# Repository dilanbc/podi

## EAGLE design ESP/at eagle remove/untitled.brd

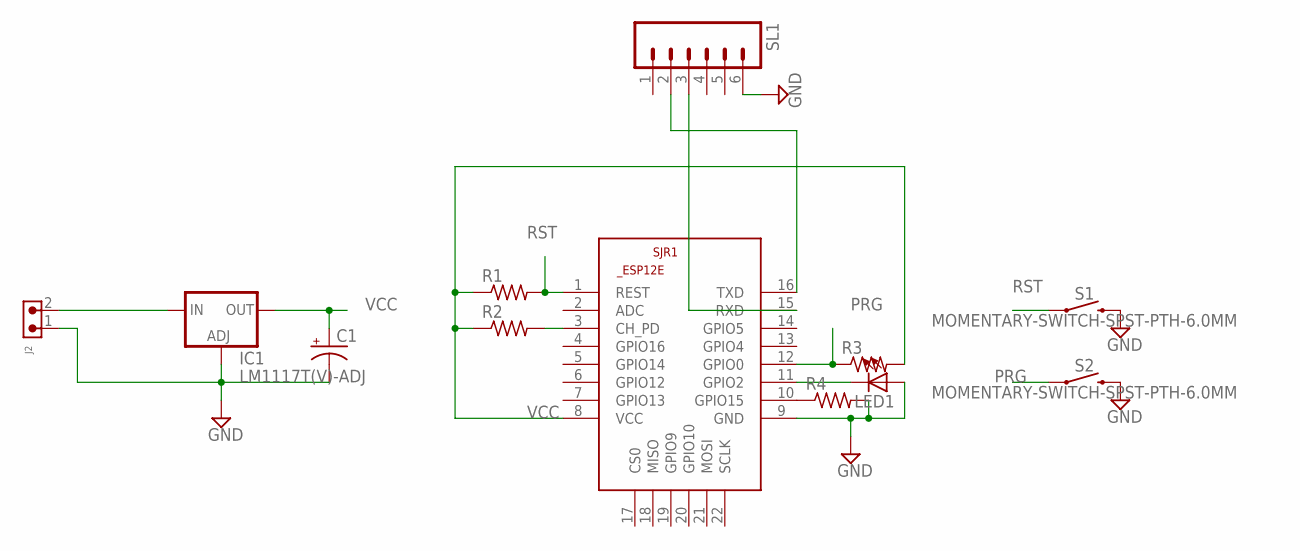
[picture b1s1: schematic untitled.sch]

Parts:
C1: CAPACITOR-PE5-10.5; E5-10,5
IC1: LM1117T(V)-ADJ; TO220V
J2: 691305530002
LED1: LED5MM
R1, R2, R3, R4: R-US_0207/10; 0207/10
S1, S2: MOMENTARY-SWITCH-SPST-PTH-6.0MM; TACTILE_SWITCH_PTH_6.0MM
SJR1: ESP8266-12EESP12E; ESP8266-ESP12E
SL1: M06; 06P

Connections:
GND: C1.-, IC1.1 (ADJ), J2.1, LED1.A, R4.2, S1.3 (2), S2.3 (2), SJR1.9 (GND), SL1.6
unnamed: IC1.3 (IN), J2.2
unnamed: R2.2, SJR1.3 (CH_PD)
unnamed: SJR1.16 (TXD), SL1.2
unnamed: SJR1.15 (RXD), SL1.3
unnamed: LED1.K (C), SJR1.11 (GPIO2)
unnamed: R4.1, SJR1.10 (GPIO15)
PRG: R3.1, S2.1, SJR1.12 (GPIO0)
RST: R1.2, S1.1, SJR1.1 (REST)
VCC: C1.+, IC1.2 (OUT), R1.1, R2.1, R3.2, SJR1.8 (VCC)

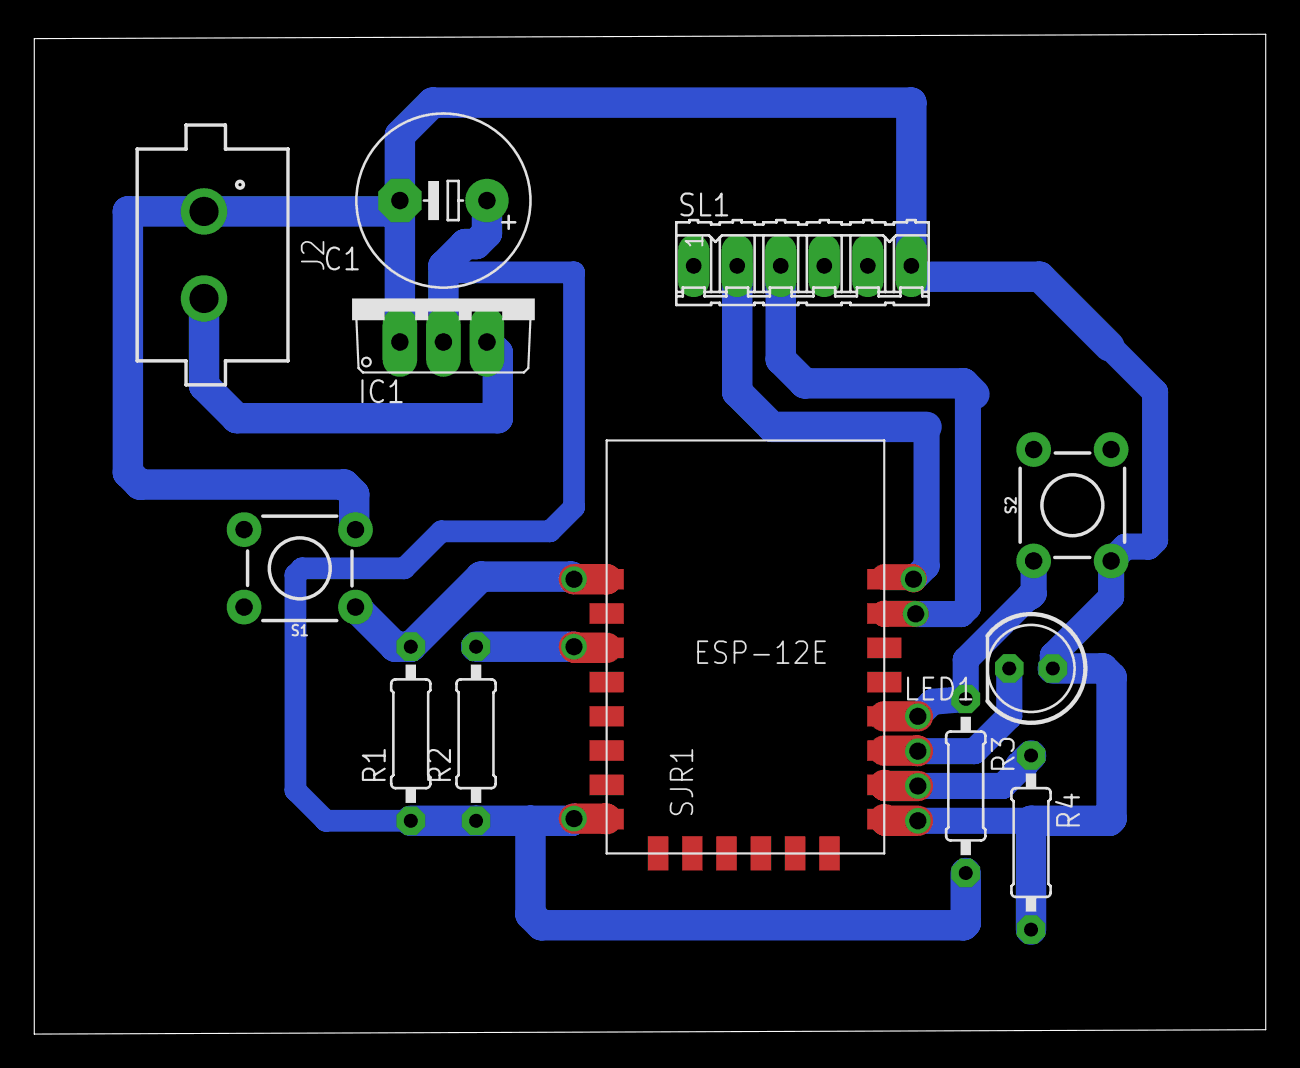
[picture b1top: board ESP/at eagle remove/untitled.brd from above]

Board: 2 copper layers, 71.9 x 58.3 mm, 12 parts (0 on the bottom side), 10 nets.

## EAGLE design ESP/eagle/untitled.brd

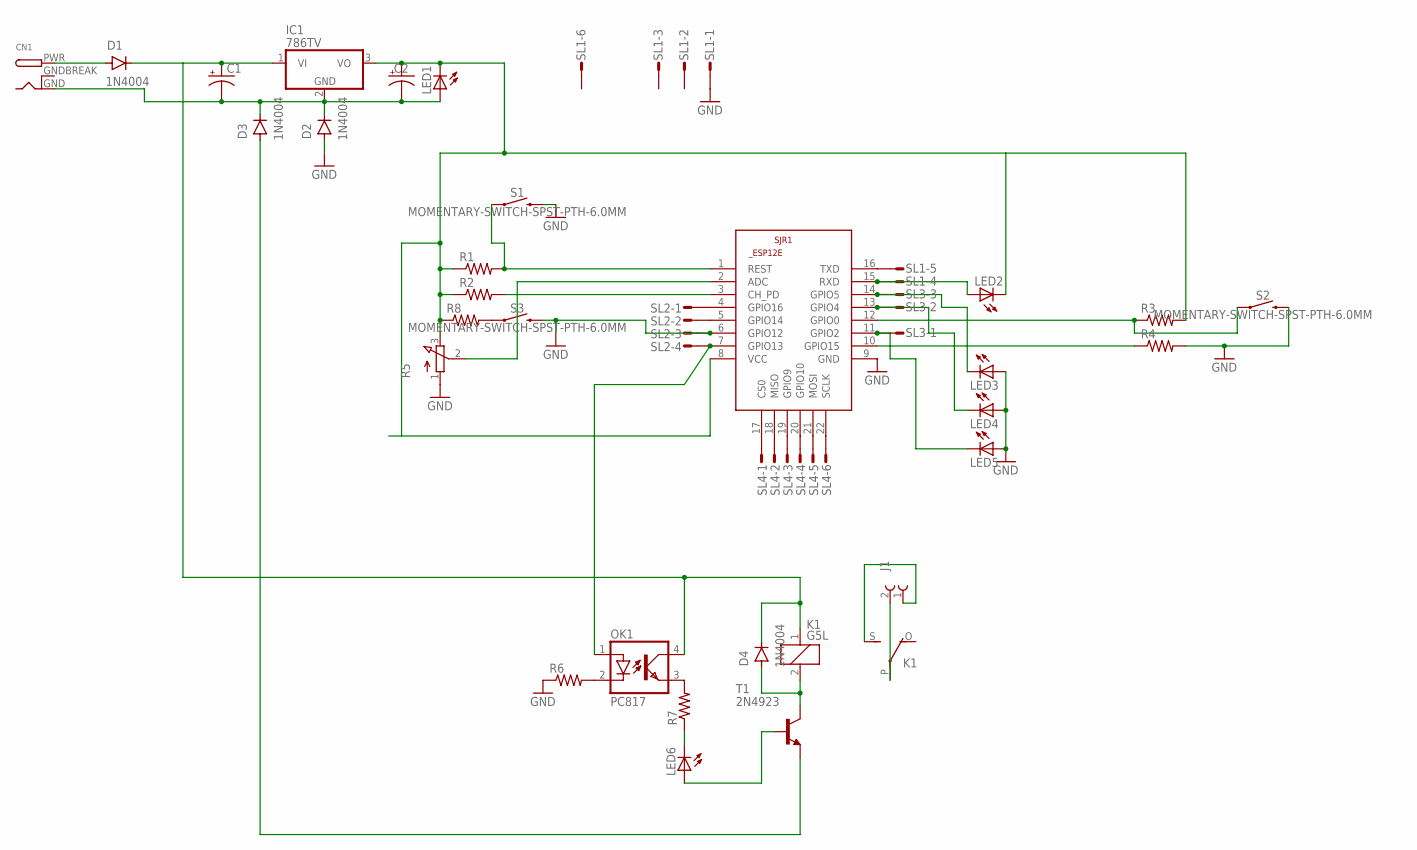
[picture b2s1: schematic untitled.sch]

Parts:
C1, C2: CAPACITOR-PE3.5-8; E3,5-8
CN1: DCBARRELPTH; DCJACK_2MM_PTH
D1, D2, D3, D4: 1N4004; DO-41
IC1: 786TV; TO220V
J1: 691370710002B
K1: G5L; G5LE
LED1, LED2, LED3, LED4, LED5, LED6: LED5MM
OK1: PC817; DIL04
R1, R2, R3, R4, R6, R7, R8: R-US_0309/10; 0309/10
R5: 3RP/1610N
S1, S2, S3: MOMENTARY-SWITCH-SPST-PTH-6.0MM; TACTILE_SWITCH_PTH_6.0MM
SJR1: ESP8266-12EESP12E; ESP8266-ESP12E
SL1, SL4: M06S; 06P
SL2: M04S; 04P
SL3: M03S; 03P
T1: 2N4923; TO126

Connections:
GND: D2.A, LED3.A, LED4.A, LED5.A, R4.2, R5.1 (A), R6.1, S1.3 (2), S2.3 (2), S3.3 (2), SJR1.6 (GPIO12), SJR1.9 (GND), SL1.1, SL2.3
GNDBREAK: CN1.GNDBREAK
unnamed: CN1.PWR, D1.A
unnamed: C1.+, D1.C, D4.C, IC1.1 (VI), K1.1, OK1.4 (COL)
unnamed: C1.-, C2.-, CN1.GND, D2.C, D3.C, IC1.2 (GND), LED1.A
unnamed: C2.+, IC1.3 (VO), LED1.K (C), LED2.K (C), R1.1, R2.1, R3.2, R5.3 (E), R8.1, SJR1.8 (VCC)
unnamed: R3.1, S2.1, SJR1.12 (GPIO0)
unnamed: R2.2, SJR1.3 (CH_PD)
unnamed: R1.2, S1.1, SJR1.1 (REST)
unnamed: R4.1, SJR1.10 (GPIO15)
unnamed: SJR1.16 (TXD), SL1.5
unnamed: LED2.A, SJR1.15 (RXD), SL1.4
unnamed: R5.2 (S), SJR1.2 (ADC)
unnamed: SJR1.4 (GPIO16), SL2.1
unnamed: SJR1.5 (GPIO14), SL2.2
unnamed: OK1.1 (A), SJR1.7 (GPIO13), SL2.4
unnamed: LED3.K (C), SJR1.14 (GPIO5), SL3.3
unnamed: LED4.K (C), SJR1.13 (GPIO4), SL3.2
unnamed: LED5.K (C), SJR1.11 (GPIO2), SL3.1
unnamed: SJR1.17 (CS0), SL4.1
unnamed: SJR1.18 (MISO), SL4.2
unnamed: SJR1.19 (GPIO9), SL4.3
unnamed: SJR1.20 (GPIO10), SL4.4
unnamed: SJR1.21 (MOSI), SL4.5
unnamed: SJR1.22 (SCLK), SL4.6
unnamed: OK1.2 (C), R6.2
unnamed: OK1.3 (EMIT), R7.2
unnamed: D3.A, T1.1 (E)
unnamed: LED6.K (C), R7.1
unnamed: LED6.A, T1.3 (B)
unnamed: J1.2 (1), K1.P
unnamed: D4.A, K1.2, T1.2 (C)
unnamed: J1.1 (2), K1.S
unnamed: R8.2, S3.1

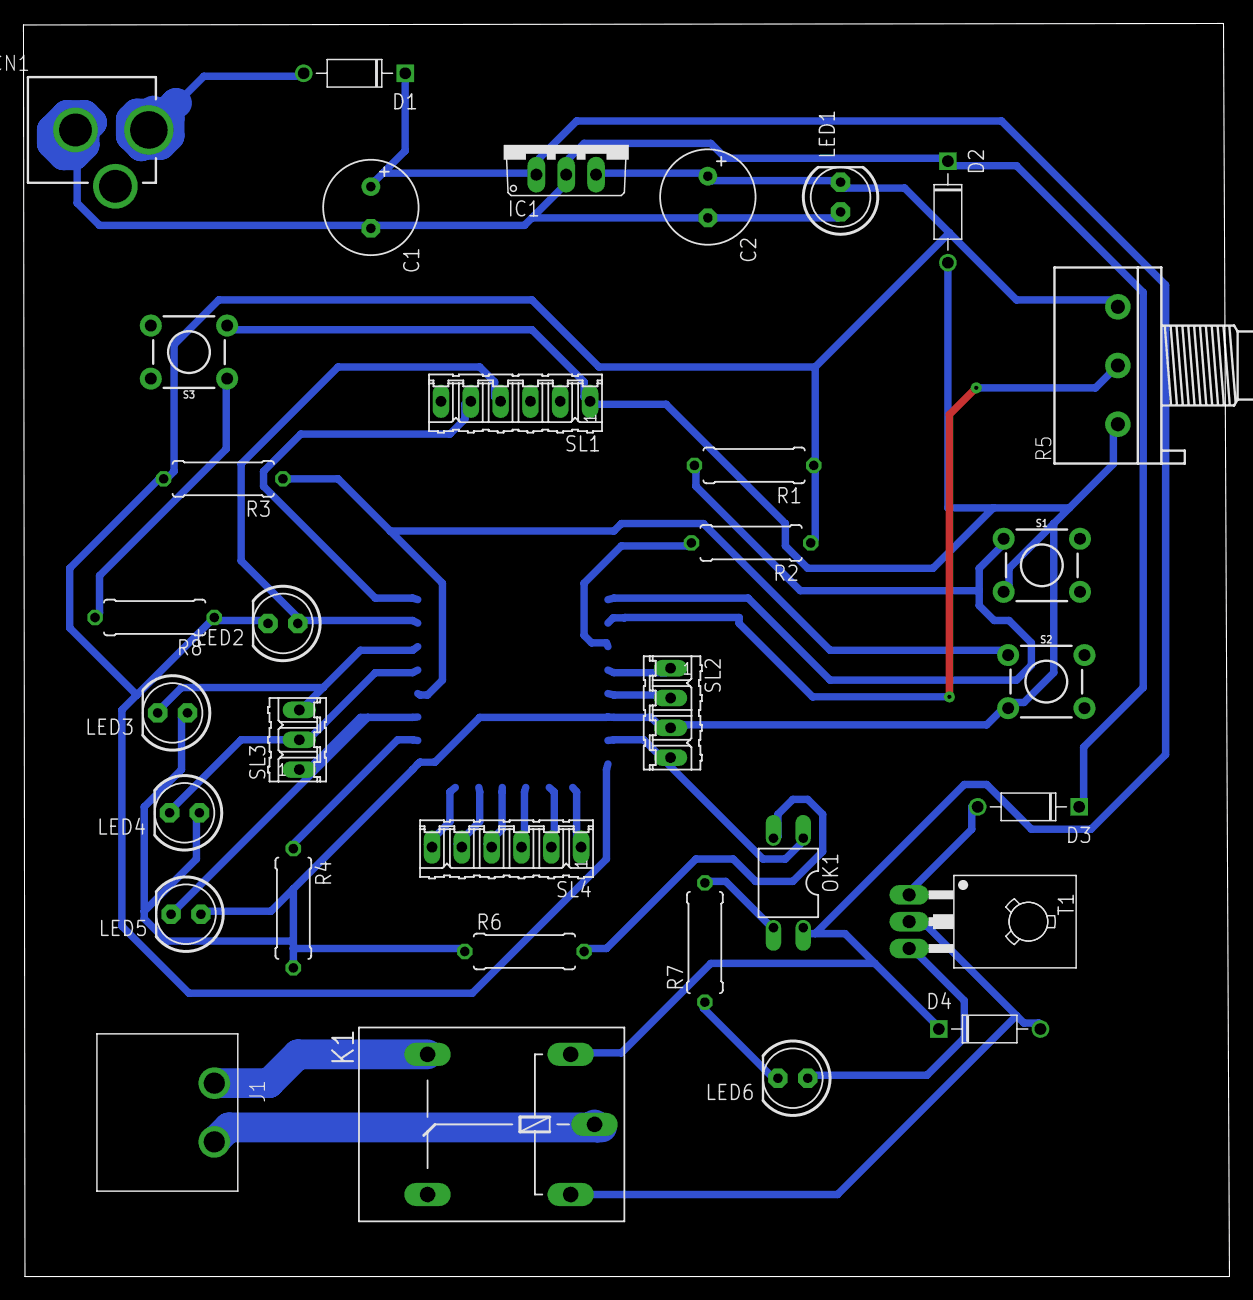
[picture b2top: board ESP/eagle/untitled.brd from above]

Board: 2 copper layers, 102.7 x 106.7 mm, 34 parts (1 on the bottom side), 33 nets.

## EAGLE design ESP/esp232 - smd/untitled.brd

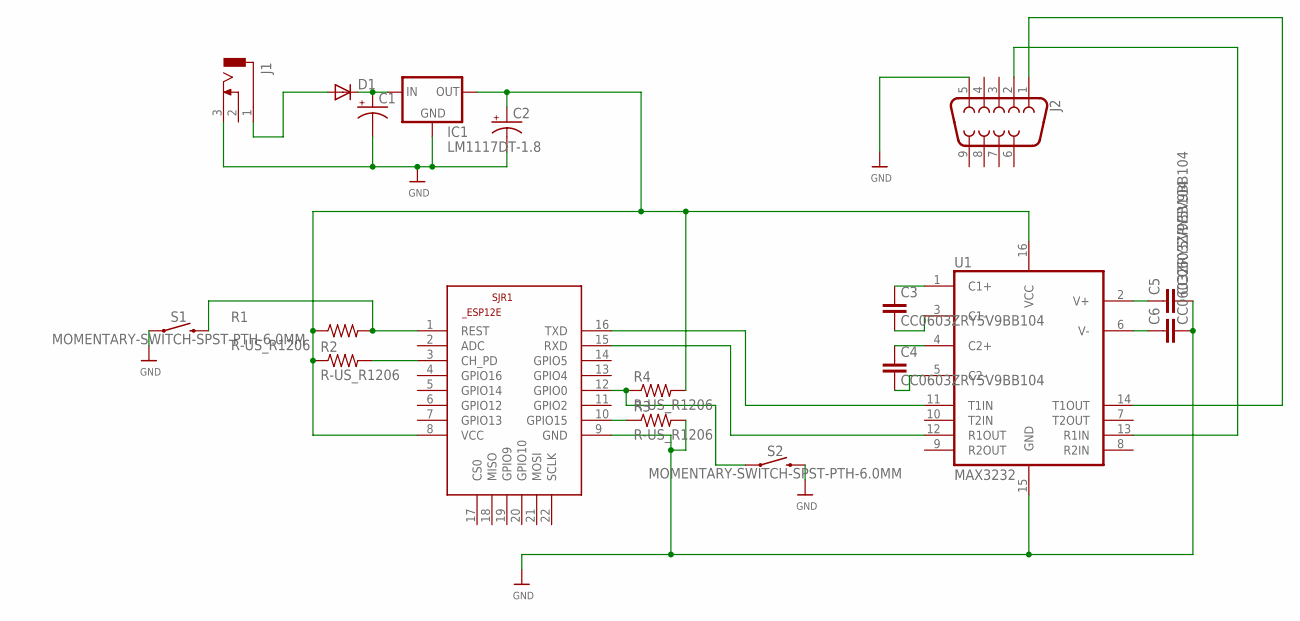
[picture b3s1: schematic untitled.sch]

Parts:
C1, C2: CPOL-US175TMP-0810; 175TMP-0810
C3, C4, C5, C6: CC0603ZRY5V9BB104
D1: DIODESMA; SMADIODE
IC1: LM1117DT-1.8; TO252
J1: DCJ0303
J2: DB9MALE; DB9_MALE
R1, R2, R3, R4: R-US_R1206; R1206
S1, S2: MOMENTARY-SWITCH-SPST-PTH-6.0MM; TACTILE_SWITCH_PTH_6.0MM
SJR1: ESP8266-12EESP12E; ESP8266-ESP12E
U1: MAX3232; SO16

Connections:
GND: C1.-, C2.-, C5.2, C6.2, IC1.1 (GND), J1.3, J2.5, R3.2, S1.1, S2.3 (2), SJR1.9 (GND), U1.15 (GND)
unnamed: R2.2, SJR1.3 (CH_PD)
unnamed: D1.A, J1.1
unnamed: C1.+, D1.C, IC1.2 (IN)
unnamed: R1.2, S1.3 (2), SJR1.1 (REST)
unnamed: R3.1, SJR1.10 (GPIO15)
unnamed: C3.1, U1.1 (C1+)
unnamed: R4.1, S2.1, SJR1.12 (GPIO0)
unnamed: C3.2, U1.3 (C1-)
unnamed: C4.1, U1.4 (C2+)
unnamed: C4.2, U1.5 (C2-)
unnamed: C5.1, U1.2 (V+)
unnamed: C6.1, U1.6 (V-)
unnamed: SJR1.16 (TXD), U1.11 (T1IN)
unnamed: SJR1.15 (RXD), U1.12 (R1OUT)
unnamed: J2.2, U1.13 (R1IN)
unnamed: J2.1, U1.14 (T1OUT)
unnamed: C2.+, IC1.3 (OUT), R1.1, R2.1, R4.2, SJR1.8 (VCC), U1.16 (VCC)

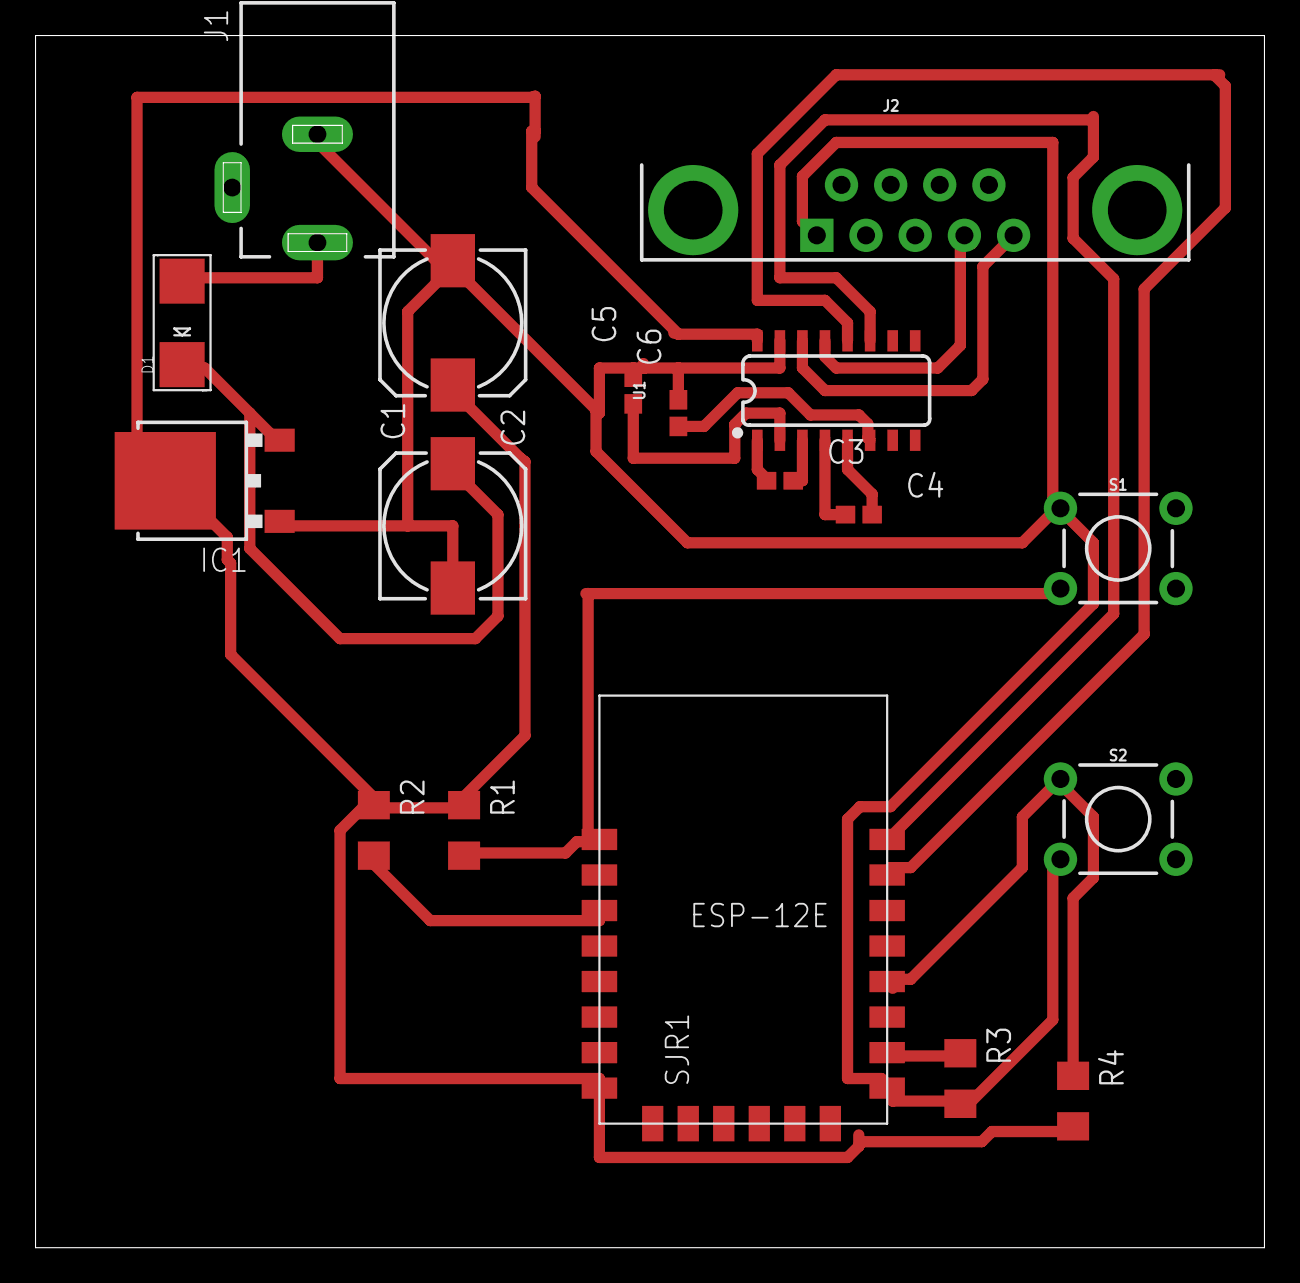
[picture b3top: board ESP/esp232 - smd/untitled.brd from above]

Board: 2 copper layers, 69.2 x 68.2 mm, 18 parts (0 on the bottom side), 18 nets.

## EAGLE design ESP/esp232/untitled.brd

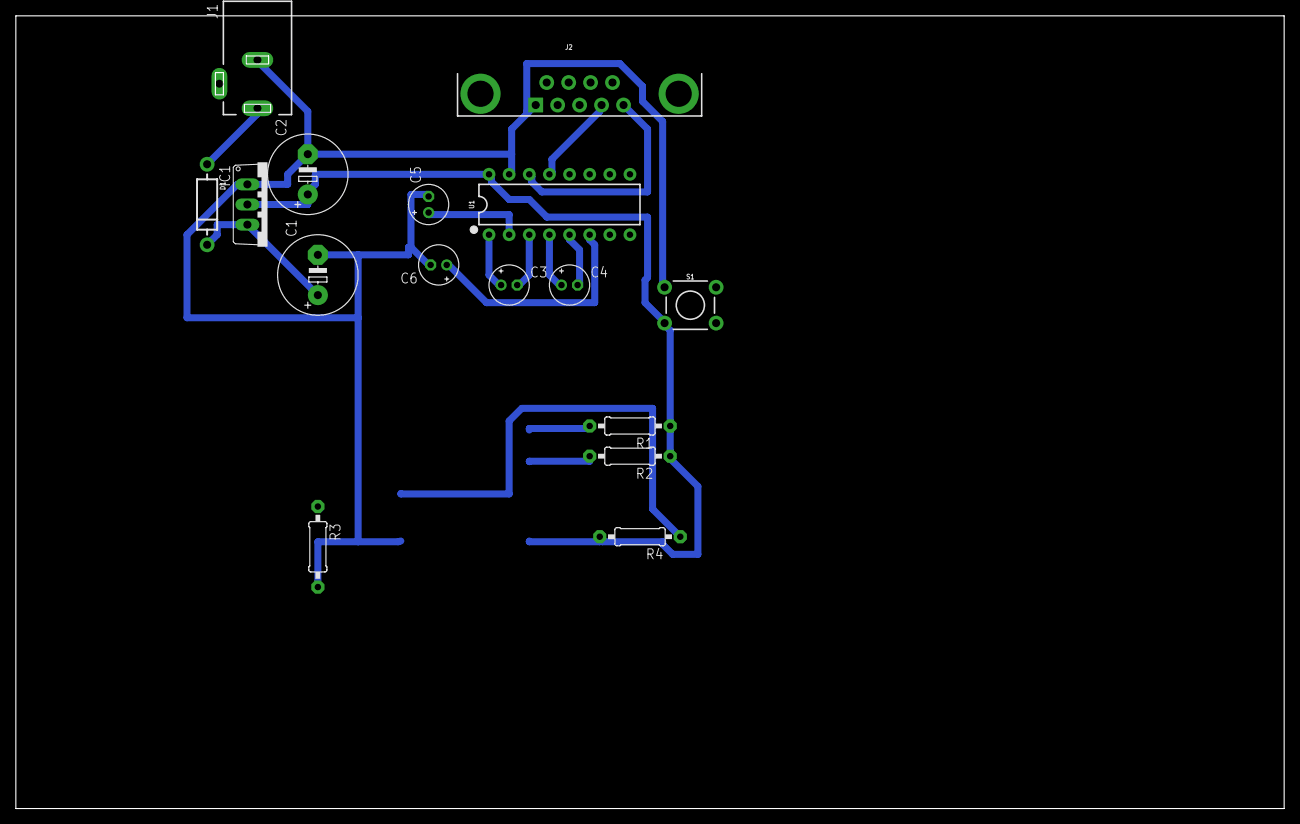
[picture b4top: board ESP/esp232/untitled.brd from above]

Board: 2 copper layers, 160.0 x 100.0 mm, 17 parts (1 on the bottom side), 18 nets.

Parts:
C1, C2: E5-10,5
C3, C4, C5, C6: E2-5
D1: DIODE-1N4001-KIT
IC1: LM1117T(V)-ADJ; TO220V
J1: DCJ0303
J2: DB9_MALE
R1, R2, R3, R4: 0207/10
S1: MOMENTARY-SWITCH-SPST-PTH-6.0MM; TACTILE_SWITCH_PTH_6.0MM
SJR1: ESP8266-ESP12E
U1: MAX3232; DIP16

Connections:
GND: C1.-, C2.-, C5.-, C6.-, IC1.1, J1.3, J2.5, R3.2, S1.1, SJR1.9, U1.15
unnamed: R2.2, SJR1.3
unnamed: D1.A, J1.1
unnamed: C1.+, D1.C, IC1.3
unnamed: C2.+, IC1.2, R1.1, R2.1, R4.2, S1.3, SJR1.8, U1.16
unnamed: R1.2, SJR1.1
unnamed: R3.1, SJR1.10
unnamed: C3.+, U1.1
unnamed: R4.1, SJR1.12
unnamed: C3.-, U1.3
unnamed: C4.+, U1.4
unnamed: C4.-, U1.5
unnamed: C5.+, U1.2
unnamed: C6.+, U1.6
unnamed: SJR1.16, U1.11
unnamed: SJR1.15, U1.12
unnamed: J2.2, U1.13
unnamed: J2.1, U1.14

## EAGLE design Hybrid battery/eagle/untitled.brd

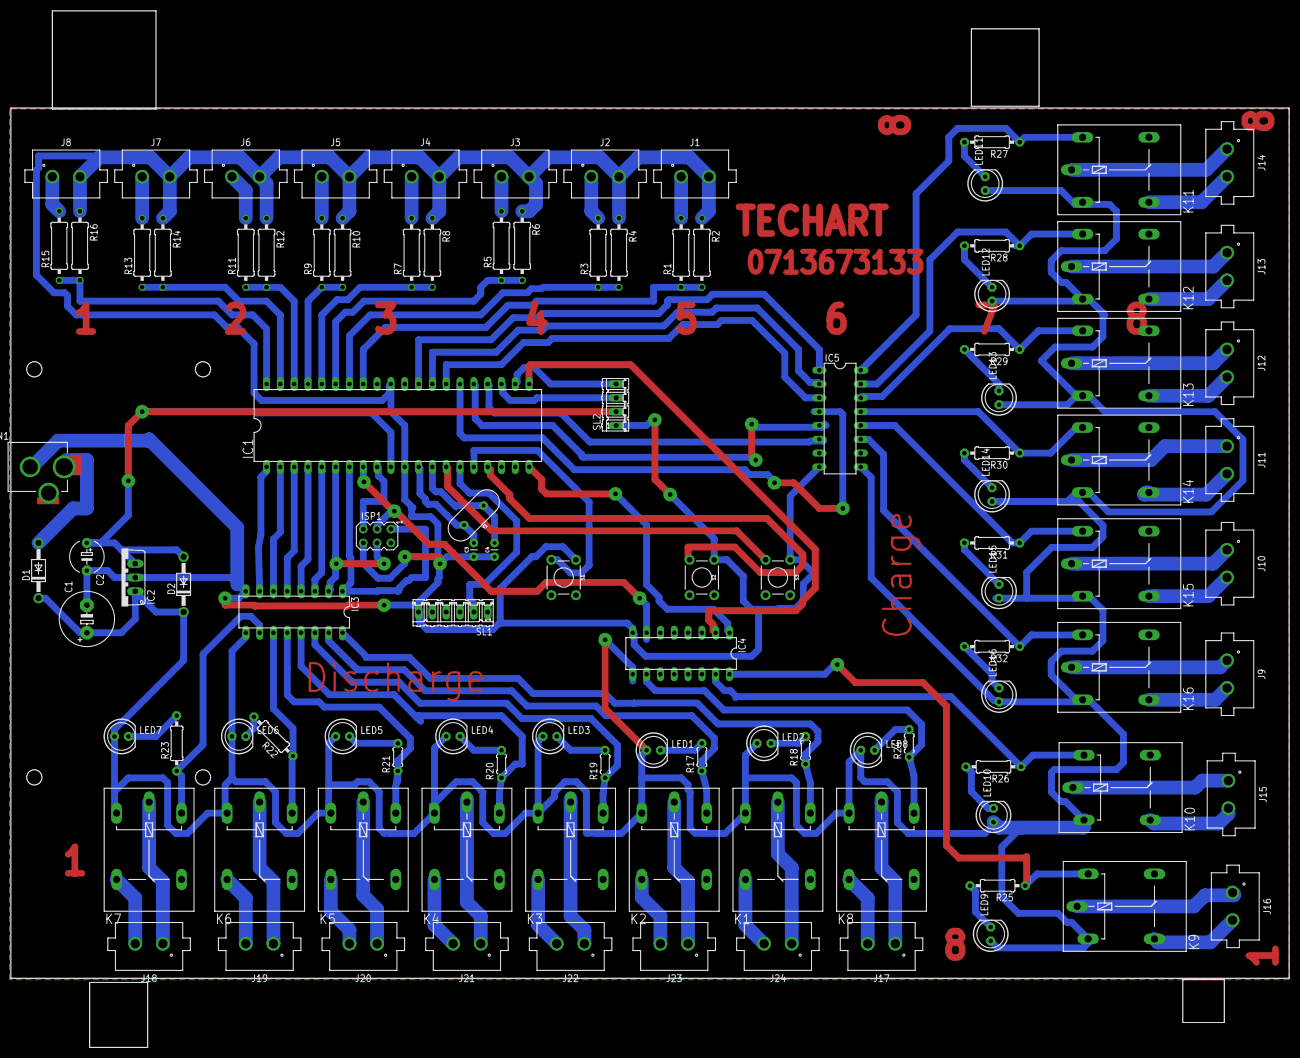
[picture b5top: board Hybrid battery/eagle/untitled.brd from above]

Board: 2 copper layers, 234.9 x 159.9 mm, 107 parts (0 on the bottom side), 109 nets.

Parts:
C1: E5-10,5
C2: E5-6
C3, C4: 22pF; CAP-PTH-2.54
CN1: DCJACK_2MM_PTH
D1, D2: 1N4004; DO41-10
IC1: MEGA16-P; DIL40
IC2: 7805TV; TO220V
IC3, IC4, IC5: ULN2003AN; DIL16
ISP1: AVRISP-6; AVRISP
J1, J2, J3, J4, J5, J6, J7, J8, J9, J10, J11, J12, J13, J14, J15, J16, J17, J18, J19, J20, J21, J22, J23, J24: 691305530002
K1, K2, K3, K4, K5, K6, K7, K8, K9, K10, K11, K12, K13, K14, K15, K16: G5L; G5LE
LED1, LED2, LED3, LED4, LED5, LED6, LED7, LED8, LED9, LED10, LED11, LED12, LED13, LED14, LED15, LED16: LED5MM
R1, R2, R3, R4, R5, R6, R7, R8, R9, R10, R11, R12, R13, R14, R15, R16: 0309/12
R17, R18, R19, R20, R21, R24: 0204/5
R22, R23, R25, R26, R27, R28, R29, R30, R31, R32: 0207/10
S1, S2, S3: MOMENTARY-SWITCH-SPST-PTH-6.0MM-KIT; TACTILE_SWITCH_PTH_6.0MM_KIT
SL1: 06P
SL2: 04P
Y1: 16MHz; HC49US

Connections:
CH0: IC1.20, IC4.1
CH1: IC1.21, IC4.2
CH2: IC1.24, IC5.6
CH3: IC1.25, IC5.5
CH4: IC1.26, IC5.4
CH5: IC1.27, IC5.3
CH6: IC1.28, IC5.2
CH7: IC1.29, IC5.1
DS0: IC1.1, IC3.7
DS1: IC1.2, IC3.6
DS2: IC1.3, IC3.5
DS3: IC1.4, IC3.4
DS4: IC1.5, IC3.3
GND: C1.-, C2.-, C3.1, C4.1, CN1.GND, IC1.11, IC1.31, IC2.2, IC3.8, IC4.8, IC5.8, ISP1.6, J1.2, J2.2, J3.2, J4.2, J5.2, J6.2, J7.2, J8.2, R2.1, R4.1, R6.1, R8.1, R10.1, R12.1, R14.1, R16.1, S1.1, S2.1, S3.1, SL1.6, SL2.1
MISO: IC1.7, IC3.1, ISP1.1
MOSI: IC1.6, IC3.2, ISP1.4
unnamed: C2.+, D2.A, IC1.10, IC2.3, SL2.2
unnamed: C1.+, D1.C, D2.C, IC2.1, IC3.9, IC4.9, IC5.9, K1.1, K2.1, K3.1, K4.1, K5.1, K6.1, K7.1, K8.1, K9.1, K10.1, K11.1, K12.1, K13.1, K14.1, K15.1, K16.1, LED1.A, LED2.A, LED3.A, LED4.A, LED5.A, LED6.A, LED7.A, LED8.A, LED9.A, LED10.A, LED11.A, LED12.A, LED13.A, LED14.A, LED15.A, LED16.A
unnamed: IC1.16, S1.3
unnamed: IC1.23, SL2.3
unnamed: C3.2, IC1.12, Y1.2
unnamed: C4.2, IC1.13, Y1.1
unnamed: IC1.22, SL2.4
unnamed: J1.1, R1.2
unnamed: IC1.17, S2.3
unnamed: IC4.10, K8.2, R24.1
unnamed: IC1.33, R1.1, R2.2
unnamed: J2.1, R3.2
unnamed: IC1.34, R3.1, R4.2
unnamed: J3.1, R5.2
unnamed: IC1.35, R5.1, R6.2
unnamed: J4.1, R7.2
unnamed: IC1.36, R7.1, R8.2
unnamed: J5.1, R9.2
unnamed: J6.1, R11.2
unnamed: IC1.38, R11.1, R12.2
unnamed: J7.1, R13.2
unnamed: IC1.39, R13.1, R14.2
unnamed: J8.1, R15.2
unnamed: IC1.40, R15.1, R16.2
unnamed: IC1.37, R9.1, R10.2
unnamed: IC1.14, S3.3
unnamed: IC4.16, K9.2, R25.1
unnamed: IC4.15, K10.2, R26.1
unnamed: IC5.16, K11.2, R27.1
unnamed: IC5.12, K15.2, R31.1
unnamed: IC3.16, K1.2, R18.1
unnamed: IC3.15, K2.2, R17.1
unnamed: IC3.14, K3.2, R19.1
unnamed: IC3.13, K4.2, R20.1
unnamed: IC3.12, K5.2, R21.1
unnamed: IC3.11, K6.2, R22.1
unnamed: IC3.10, K7.2, R23.1
unnamed: IC5.13, K14.2, R30.1
unnamed: IC5.14, K13.2, R29.1
unnamed: IC5.15, K12.2, R28.1
unnamed: IC5.11, K16.2, R32.1
unnamed: J9.2, K16.S
unnamed: J9.1, K16.P
unnamed: J10.1, K15.P
unnamed: J10.2, K15.S
unnamed: J11.1, K14.P
unnamed: J11.2, K14.S
unnamed: J12.1, K13.P
unnamed: J12.2, K13.S
unnamed: J13.1, K12.P
unnamed: CN1.PWR, D1.A
unnamed: J13.2, K12.S
unnamed: J14.1, K11.P
unnamed: J14.2, K11.S
unnamed: J15.1, K10.P
unnamed: J15.2, K10.S
unnamed: J16.1, K9.P
unnamed: J16.2, K9.S
unnamed: J17.1, K8.P
unnamed: J17.2, K8.S
unnamed: J18.1, K7.P
unnamed: J18.2, K7.S
unnamed: J19.1, K6.P
unnamed: J19.2, K6.S
unnamed: J20.1, K5.P
unnamed: J20.2, K5.S
unnamed: J21.1, K4.P
unnamed: J21.2, K4.S
unnamed: J22.1, K3.P
unnamed: J22.2, K3.S
unnamed: J23.1, K2.P
unnamed: J23.2, K2.S
unnamed: J24.1, K1.P
unnamed: J24.2, K1.S
unnamed: LED2.K, R18.2
unnamed: LED1.K, R17.2
unnamed: LED3.K, R19.2
unnamed: LED4.K, R20.2
unnamed: LED5.K, R21.2
unnamed: LED6.K, R22.2
unnamed: LED7.K, R23.2
unnamed: LED8.K, R24.2
unnamed: LED9.K, R25.2
unnamed: LED10.K, R26.2
unnamed: LED11.K, R27.2
unnamed: LED12.K, R28.2
unnamed: LED13.K, R29.2
unnamed: LED14.K, R30.2
unnamed: LED15.K, R31.2
unnamed: LED16.K, R32.2
RST: IC1.9, ISP1.5
SCK: IC1.8, IC4.7, ISP1.3
TX: IC1.15, SL1.2

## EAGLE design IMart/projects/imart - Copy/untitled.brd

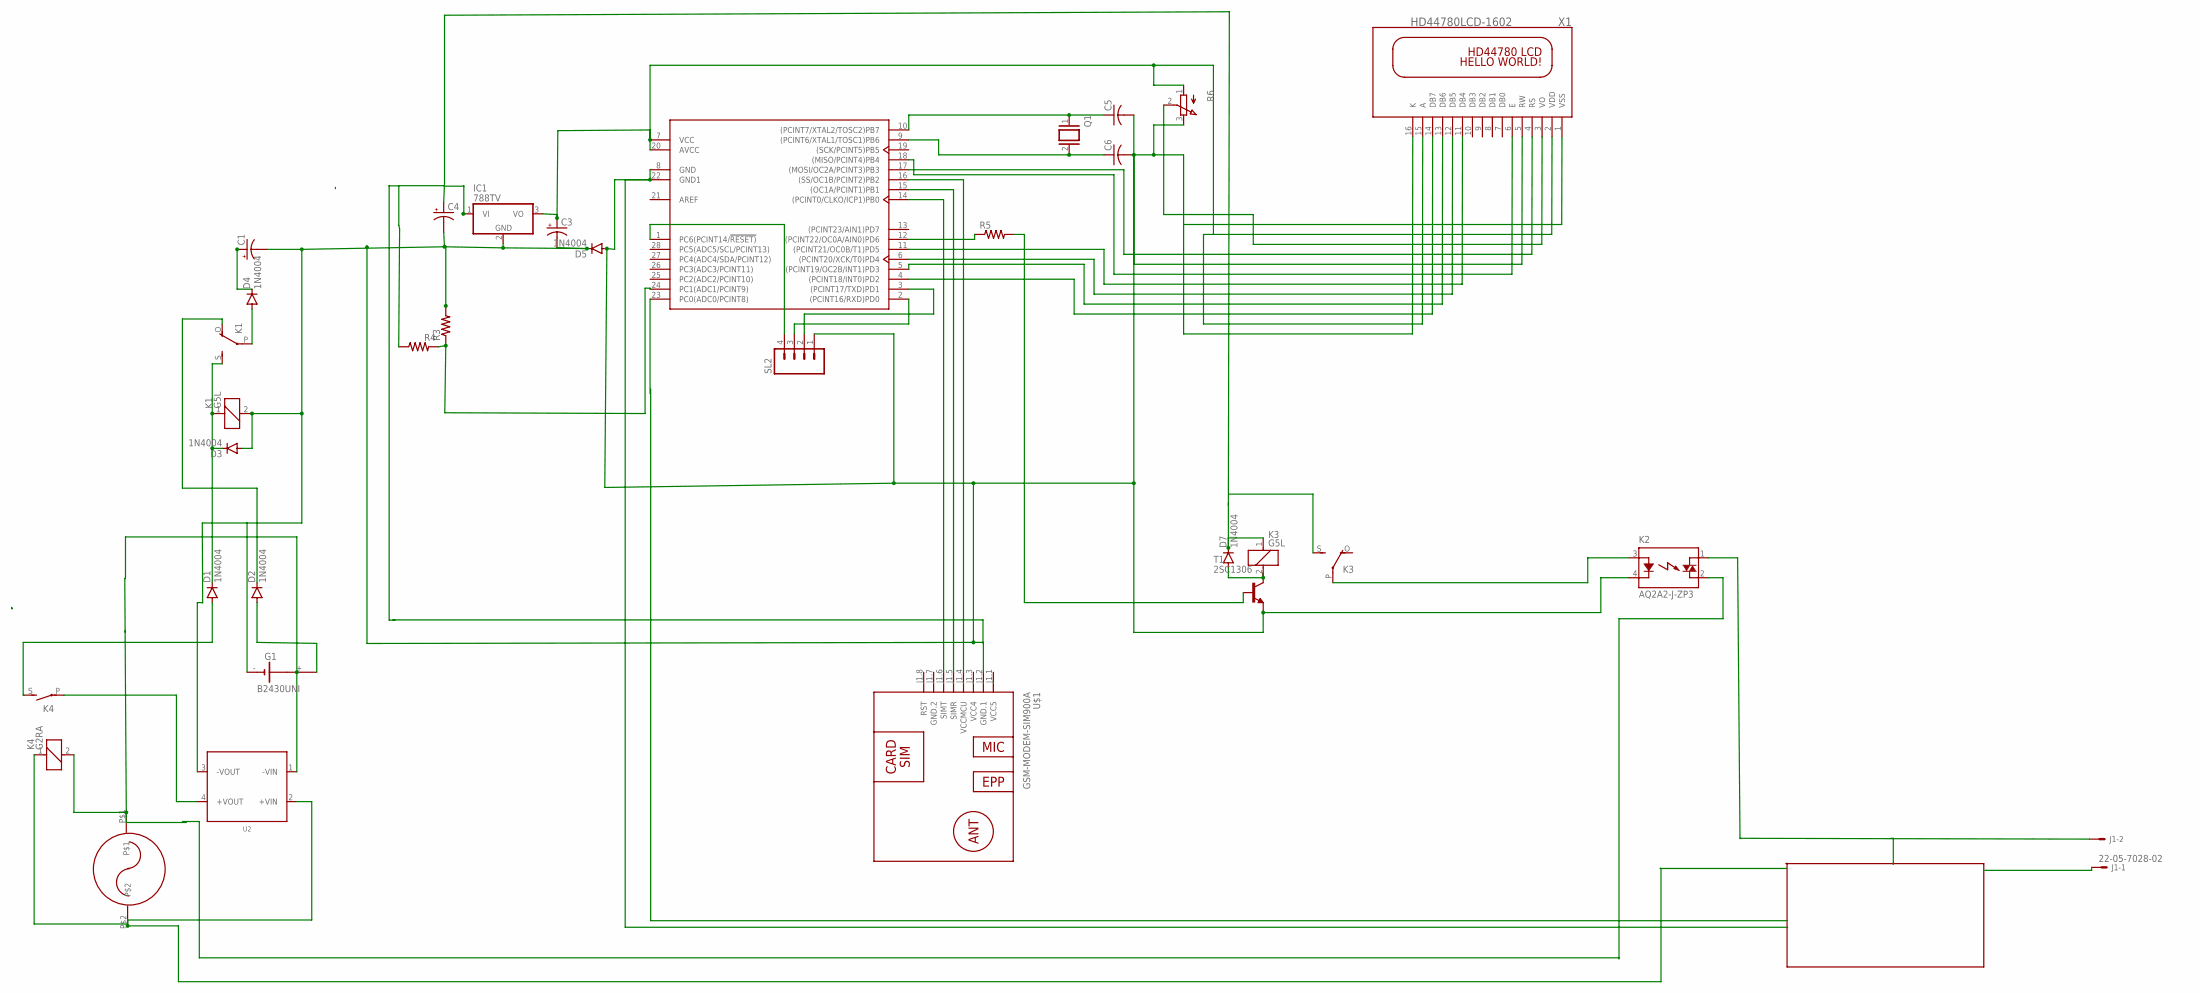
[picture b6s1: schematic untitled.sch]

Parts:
C1: CPOL-USE10-20; EB20D
C3: CPOL-USE2-5; E2-5
C4: CPOL-USE5-8.5; E5-8,5
C5, C6: C-US025-025X050; C025-025X050
D1, D2, D3, D4, D5, D7: 1N4004; DO41-10
G1: B2430UNI
IC1: 788TV; TO220V
J1: 22-05-7028-02; 7395-02
K1, K3: G5L; G5LE
K2: AQ2A2-J-ZP3; AQ1-FLAT
K4: G2RA
Q1: XTAL; Q
R3, R4, R5: R-US_0207/7; 0207/7
R6: 3RP/1610N
SL2: M04; 04P
T1: 2SC1306; TO220BV
U1: ATMEGA328P-PU; DIP-28
U2: MAGI³C-FISM_SIP-4_177920501; MAGI³C-FISM_SIP-4
U$1: GSM-MODEM-SIM900A
U$13: AC230.; AC230
X1: HD44780LCD-1602; LCD1602

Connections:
GND.2: U$1.J1.7 (GND.2)
unnamed: D1.A, K4.S
unnamed: D2.A, G1.+
unnamed: D2.C, K1.O
unnamed: D1.C, D3.C, K1.1, K1.S
unnamed: D4.A, K1.P
unnamed: R5.1, U1.12 ((PCINT22/OC0A/AIN0)PD6)
unnamed: C1.-, C3.-, C4.-, D3.A, D5.C, G1.-, IC1.2 (GND), K1.2
unnamed: C6.1, Q1.2, U1.9 ((PCINT6/XTAL1/TOSC1)PB6)
unnamed: C5.1, Q1.1, U1.10 ((PCINT7/XTAL2/TOSC2)PB7)
unnamed: G1.+@2 (+), K4.2, U2.1 (-VIN), U$13.P$1
unnamed: U1.11 ((PCINT21/OC0B/T1)PD5), X1.11 (DB4)
unnamed: R6.2 (S), X1.3 (VO)
unnamed: U1.17 ((MOSI/OC2A/PCINT3)PB3), X1.4 (RS)
unnamed: U1.18 ((MISO/PCINT4)PB4), X1.6 (E)
unnamed: U1.6 ((PCINT20/XCK/T0)PD4), X1.12 (DB5)
unnamed: U1.5 ((PCINT19/OC2B/INT1)PD3), X1.13 (DB6)
unnamed: U1.4 ((PCINT18/INT0)PD2), X1.14 (DB7)
unnamed: K2.3 (A), K3.P
unnamed: R3.1, R4.2, U1.24 (PC1(ADC1/PCINT9))
unnamed: J1.2, K2.1 (DS1)
unnamed: R5.2, T1.1 (B)
unnamed: D7.A, K3.2, T1.2 (C)
unnamed: SL2.4, U1.1 (PC6(PCINT14/!RESET))
unnamed: SL2.3, U1.2 ((PCINT16/RXD)PD0)
unnamed: SL2.2, U1.3 ((PCINT17/TXD)PD1)
unnamed: U1.14 ((PCINT0/CLKO/ICP1)PB0), U$1.J1.6 (SIMT)
unnamed: U1.15 ((OC1A/PCINT1)PB1), U$1.J1.5 (SIMR)
unnamed: U1.16 ((SS/OC1B/PCINT2)PB2), U$1.J1.4 (VCCMCU)
unnamed: D7.C, K3.1
unnamed: C1.+, D4.C
unnamed: K4.P, U2.4 (+VOUT)
unnamed: K4.1, U2.2 (+VIN), U$13.P$2
VCC4: U$1.J1.3 (VCC4)
VCC5: U$1.J1.1 (VCC5)
VDD: C3.+, IC1.3 (VO), R6.1 (A), U1.7 (VCC), U1.20 (AVCC), X1.2 (VDD), X1.15 (A)
VSS: C5.2, C6.2, D5.A, K2.4 (K), R6.3 (E), SL2.1, T1.3 (E), U1.8 (GND), U1.22 (GND1), U$1.J1.2 (GND.1), X1.1 (VSS), X1.5 (RW), X1.16 (K)

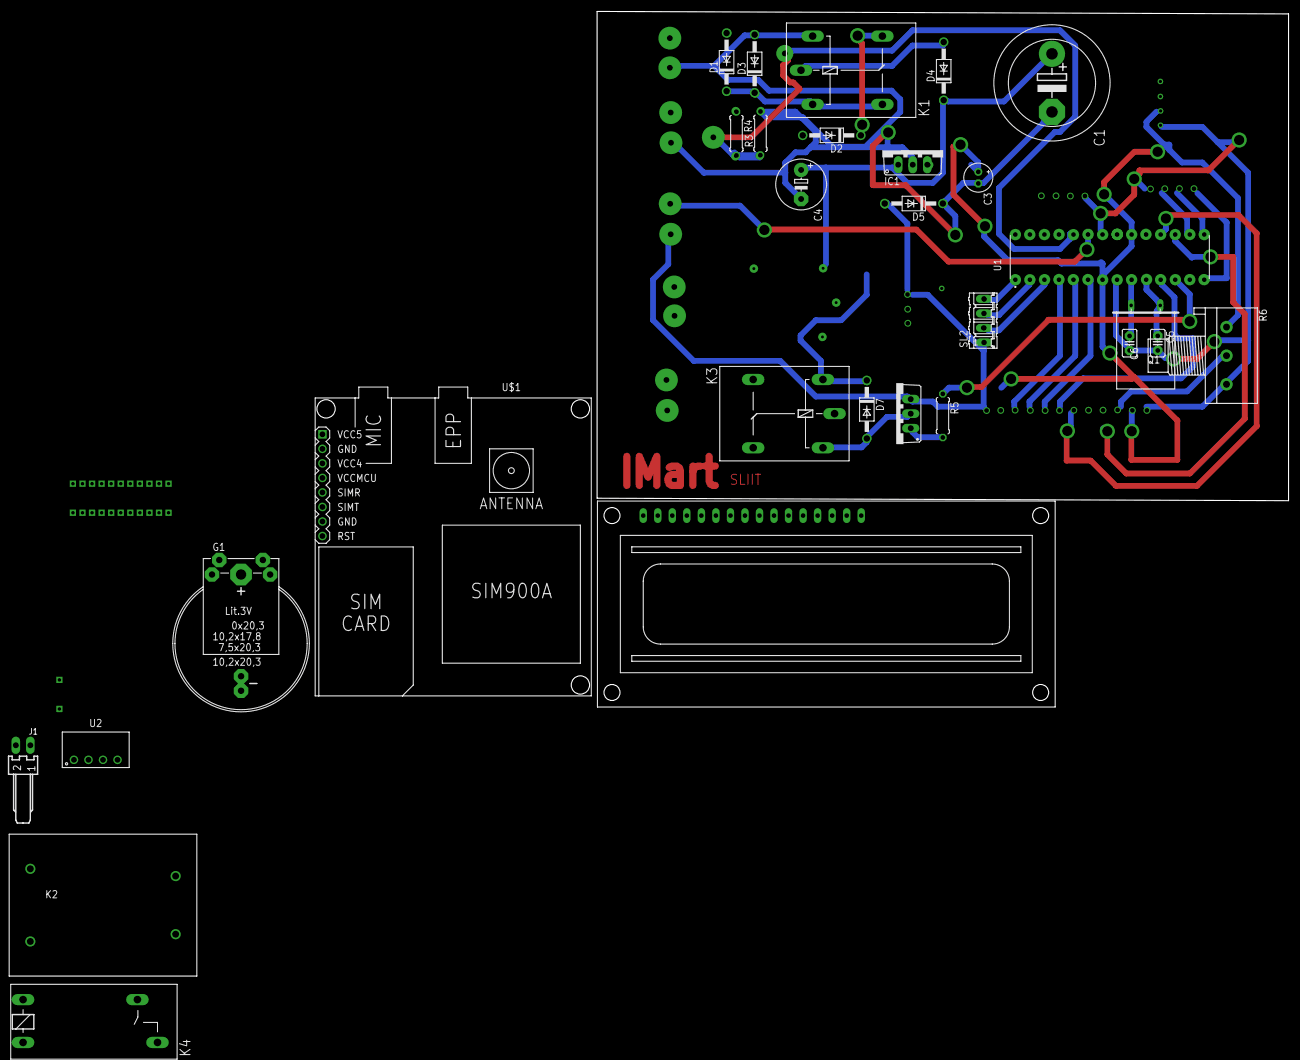
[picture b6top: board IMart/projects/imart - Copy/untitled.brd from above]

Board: 2 copper layers, 120.9 x 85.5 mm, 41 parts (0 on the bottom side), 34 nets.

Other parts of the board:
U$2, U$3, U$4, U$5, U$6, U$7, U$8, U$9, U$10, U$11, U$12: AC230.; AC230

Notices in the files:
parts and their libraries:
SparkFun-Switches: Licensing: Creative Commons ShareAlike 4.0 International - https://creativecommons.org/licenses/by-sa/4.0
Wurth_Connectors_WR-TBL Pluggable Connec: Copyright: Würth Elektronik
